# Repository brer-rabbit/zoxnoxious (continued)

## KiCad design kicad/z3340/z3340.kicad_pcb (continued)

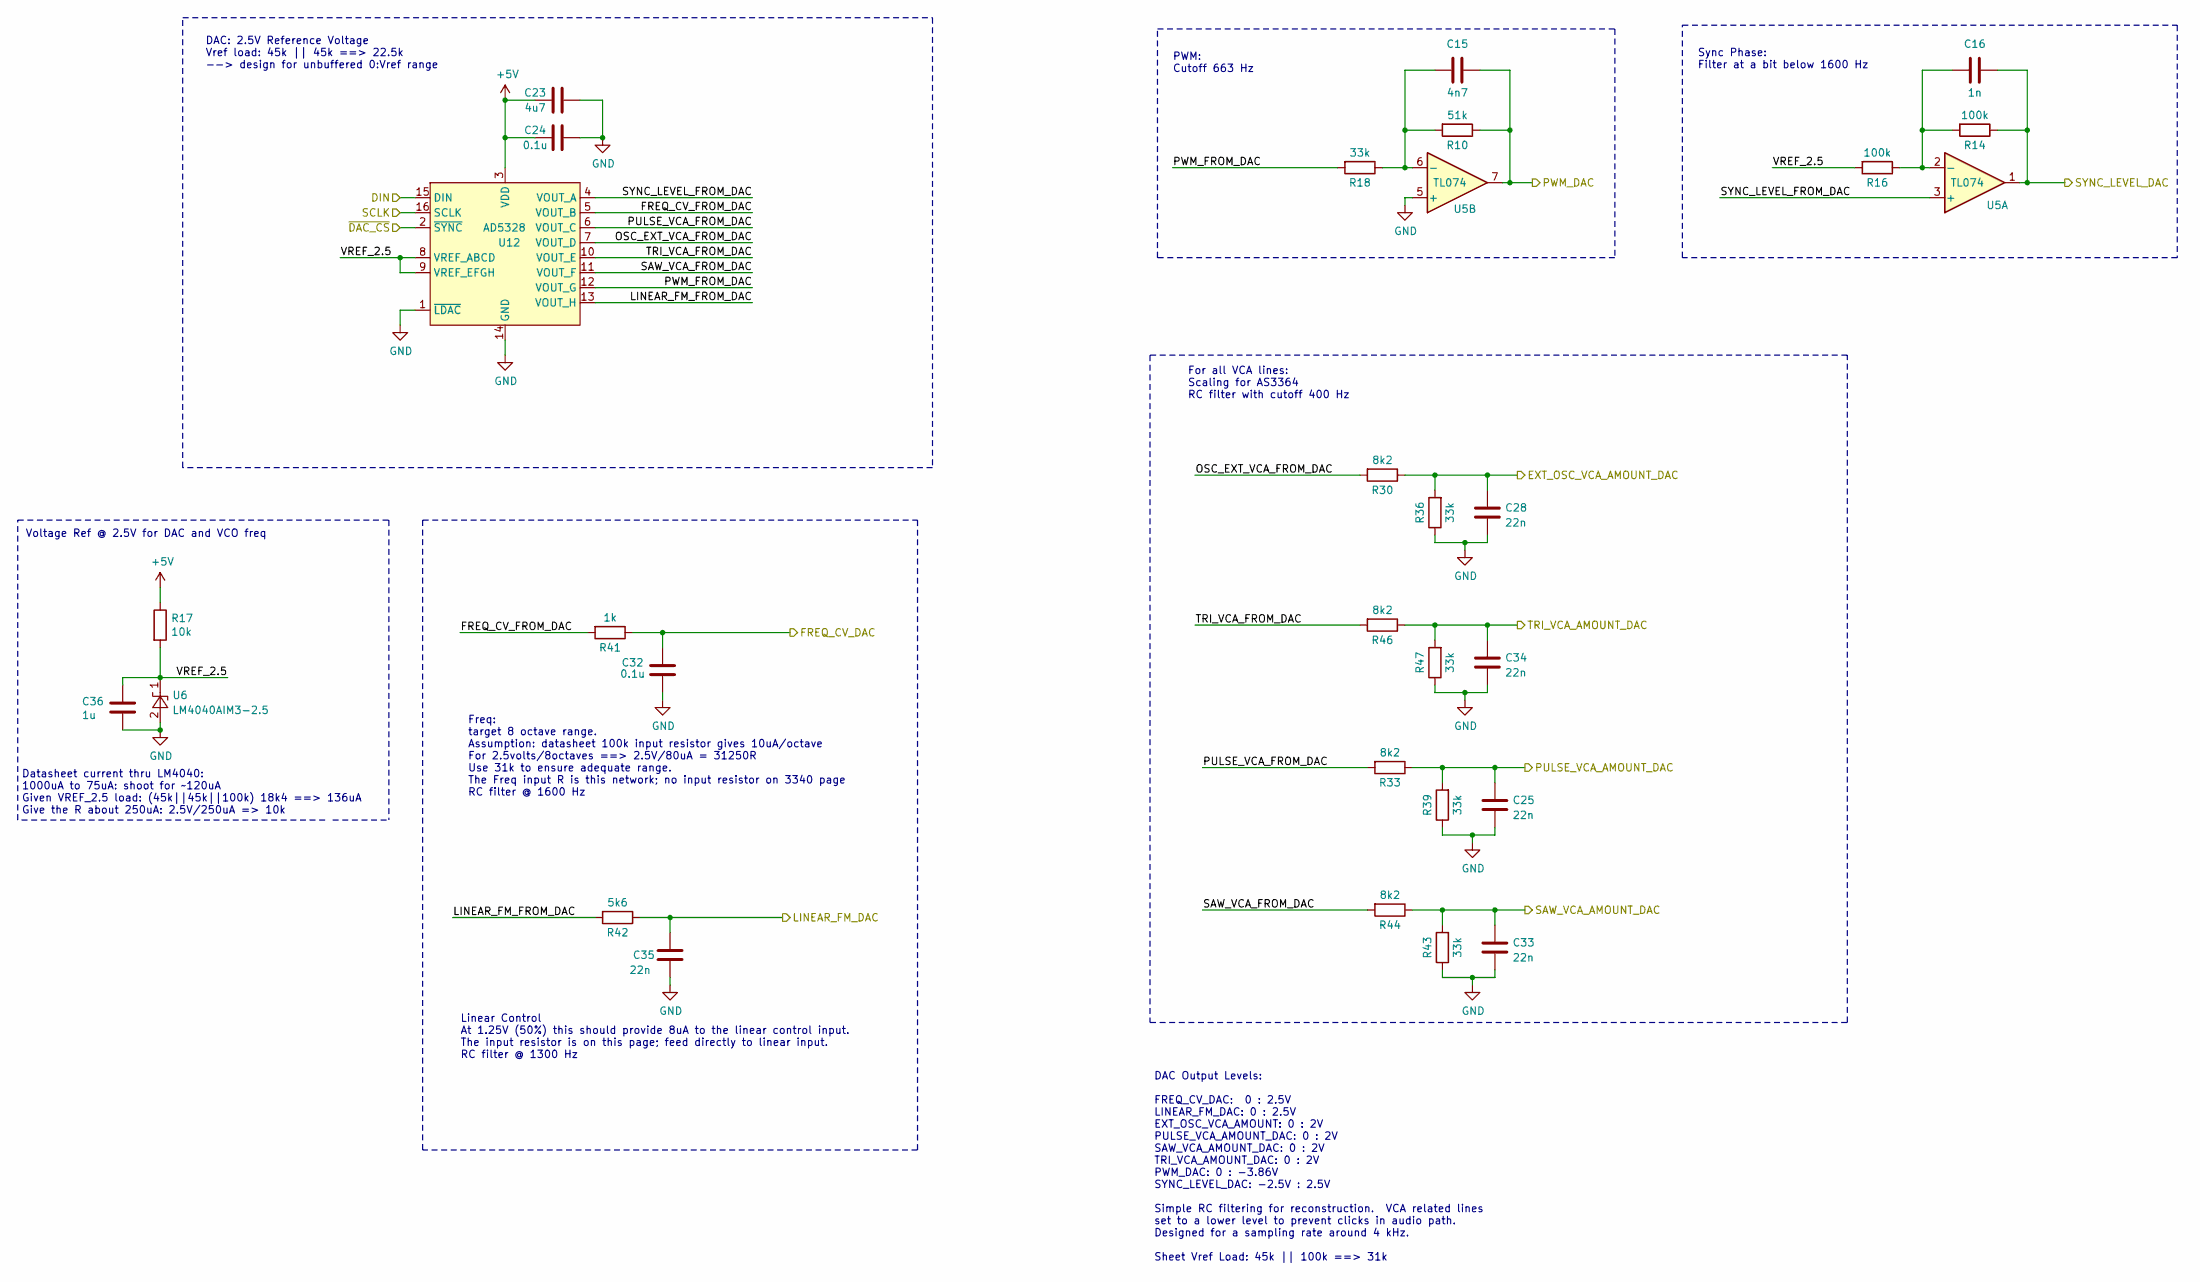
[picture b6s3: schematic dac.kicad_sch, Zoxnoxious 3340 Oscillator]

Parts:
C15: 4n7; C_0603_1608Metric; LCSC C53987
C16: 1n; C_0603_1608Metric; LCSC C1588
C23: 4u7; C_0805_2012Metric; LCSC C1779
C24, C32: 0.1u; C_0603_1608Metric; LCSC C14663
C25, C28, C33, C34, C35: 22n; C_0603_1608Metric; LCSC C21122
C36: 1u; C_0603_1608Metric; LCSC C15849
R10: 51k; R_0603_1608Metric; LCSC C23196
R14, R16: 100k; R_0603_1608Metric; LCSC C25803
R17: 10k; R_0603_1608Metric; LCSC C25804
R18, R36, R39, R43, R47: 33k; R_0603_1608Metric; LCSC C4216
R30, R33, R44, R46: 8k2; R_0603_1608Metric; LCSC C25981
R41: 1k; R_0603_1608Metric; LCSC C21190
R42: 5k6; R_0603_1608Metric; LCSC C23189
U5: TL074; TSSOP-14_4.4x5mm_P0.65mm; LCSC C96507
U6: LM4040AIM3-2.5; SOT-23; LCSC C460725
U12: AD5328; TSSOP-16_4.4x5mm_P0.65mm; LCSC C29162

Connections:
+5V: C23.1, C24.1, R17.1, U12.3 (VDD); also elsewhere on the board
/DAC/FREQ_CV_FROM_DAC: R41.2, U12.5 (VOUT_B)
/DAC/LINEAR_FM_FROM_DAC: R42.2, U12.13 (VOUT_H)
/DAC/OSC_EXT_VCA_FROM_DAC: R30.2, U12.7 (VOUT_D)
/DAC/PULSE_VCA_FROM_DAC: R33.2, U12.6 (VOUT_C)
/DAC/PWM_FROM_DAC: R18.2, U12.12 (VOUT_G)
/DAC/SAW_VCA_FROM_DAC: R44.2, U12.11 (VOUT_F)
/DAC/SYNC_LEVEL_FROM_DAC: U5.3 (+), U12.4 (VOUT_A)
/DAC/TRI_VCA_FROM_DAC: R46.2, U12.10 (VOUT_E)
/DAC/VREF_2.5: C36.1, R16.2, R17.2, U6.1 (K), U12.8 (VREF_ABCD), U12.9 (VREF_EFGH)
/EXT_OSC_VCA_AMOUNT_DAC: C28.1, R30.1, R36.2; also elsewhere on the board
/LINEAR_FM_DAC: C35.2, R42.1; also elsewhere on the board
/OSC_CV_DAC: C32.2, R41.1; also elsewhere on the board
/PULSE_VCA_AMOUNT_DAC: C25.1, R33.1, R39.2; also elsewhere on the board
/PWM_DAC: C15.2, R10.1, U5.7; also elsewhere on the board
/SAW_VCA_AMOUNT_DAC: C33.1, R43.2, R44.1; also elsewhere on the board
/SPI_CLK: U12.16 (SCLK); also elsewhere on the board
/SPI_CS0: U12.2 (~SYNC); also elsewhere on the board
/SPI_MOSI: U12.15 (DIN); also elsewhere on the board
/SYNC_LEVEL_DAC: C16.2, R14.1, U5.1; also elsewhere on the board
/TRI_VCA_AMOUNT_DAC: C34.1, R46.1, R47.2; also elsewhere on the board
GND: C23.2, C24.2, C25.2, C28.2, C32.1, C33.2, C34.2, C35.1, C36.2, R36.1, R39.1, R43.1, R47.1, U5.5 (+), U6.2 (A), U12.1 (~LDAC), U12.14 (GND); also elsewhere on the board
unnamed: C16.1, R14.2, R16.1, U5.2 (-)
unnamed: C15.1, R10.2, R18.1, U5.6 (-)

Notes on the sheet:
Linear Control At 1.25V (50%) this should provide 8uA to the linear control input. The input resistor is on this page; feed directly to linear input. RC filter @ 1300 Hz
Sync Phase: Filter at a bit below 1600 Hz
Voltage Ref @ 2.5V for DAC and VCO freq
PWM: Cutoff 663 Hz
DAC Output Levels: FREQ_CV_DAC: 0 : 2.5V LINEAR_FM_DAC: 0 : 2.5V EXT_OSC_VCA_AMOUNT: 0 : 2V PULSE_VCA_AMOUNT_DAC: 0 : 2V SAW_VCA_AMOUNT_DAC: 0 : 2V TRI_VCA_AMOUNT_DAC: 0 : 2V PWM_DAC: 0 : -3.86V SYNC_LEVEL_DAC: -2.5V : 2.5V Simple RC filtering for reconstruction. VCA related lines set to a lower le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
Datasheet current thru LM4040: 1000uA to 75uA: shoot for ~120uA Given VREF_2.5 load: (45k||45k||100k) 18k4 ==> 136uA Give the R about 250uA: 2.5V/250uA => 10k
Freq: target 8 octave range. Assumption: datasheet 100k input resistor gives 10uA/octave For 2.5volts/8octaves ==> 2.5V/80uA = 31250R Use 31k to ensure adequate range. The Freq input R is this network; no input resistor on 3340 page RC filter @ 1600 Hz
For all VCA lines: Scaling for AS3364 RC filter with cutoff 400 Hz
DAC: 2.5V Reference Voltage Vref load: 45k || 45k ==> 22.5k --> design for unbuffered 0:Vref range

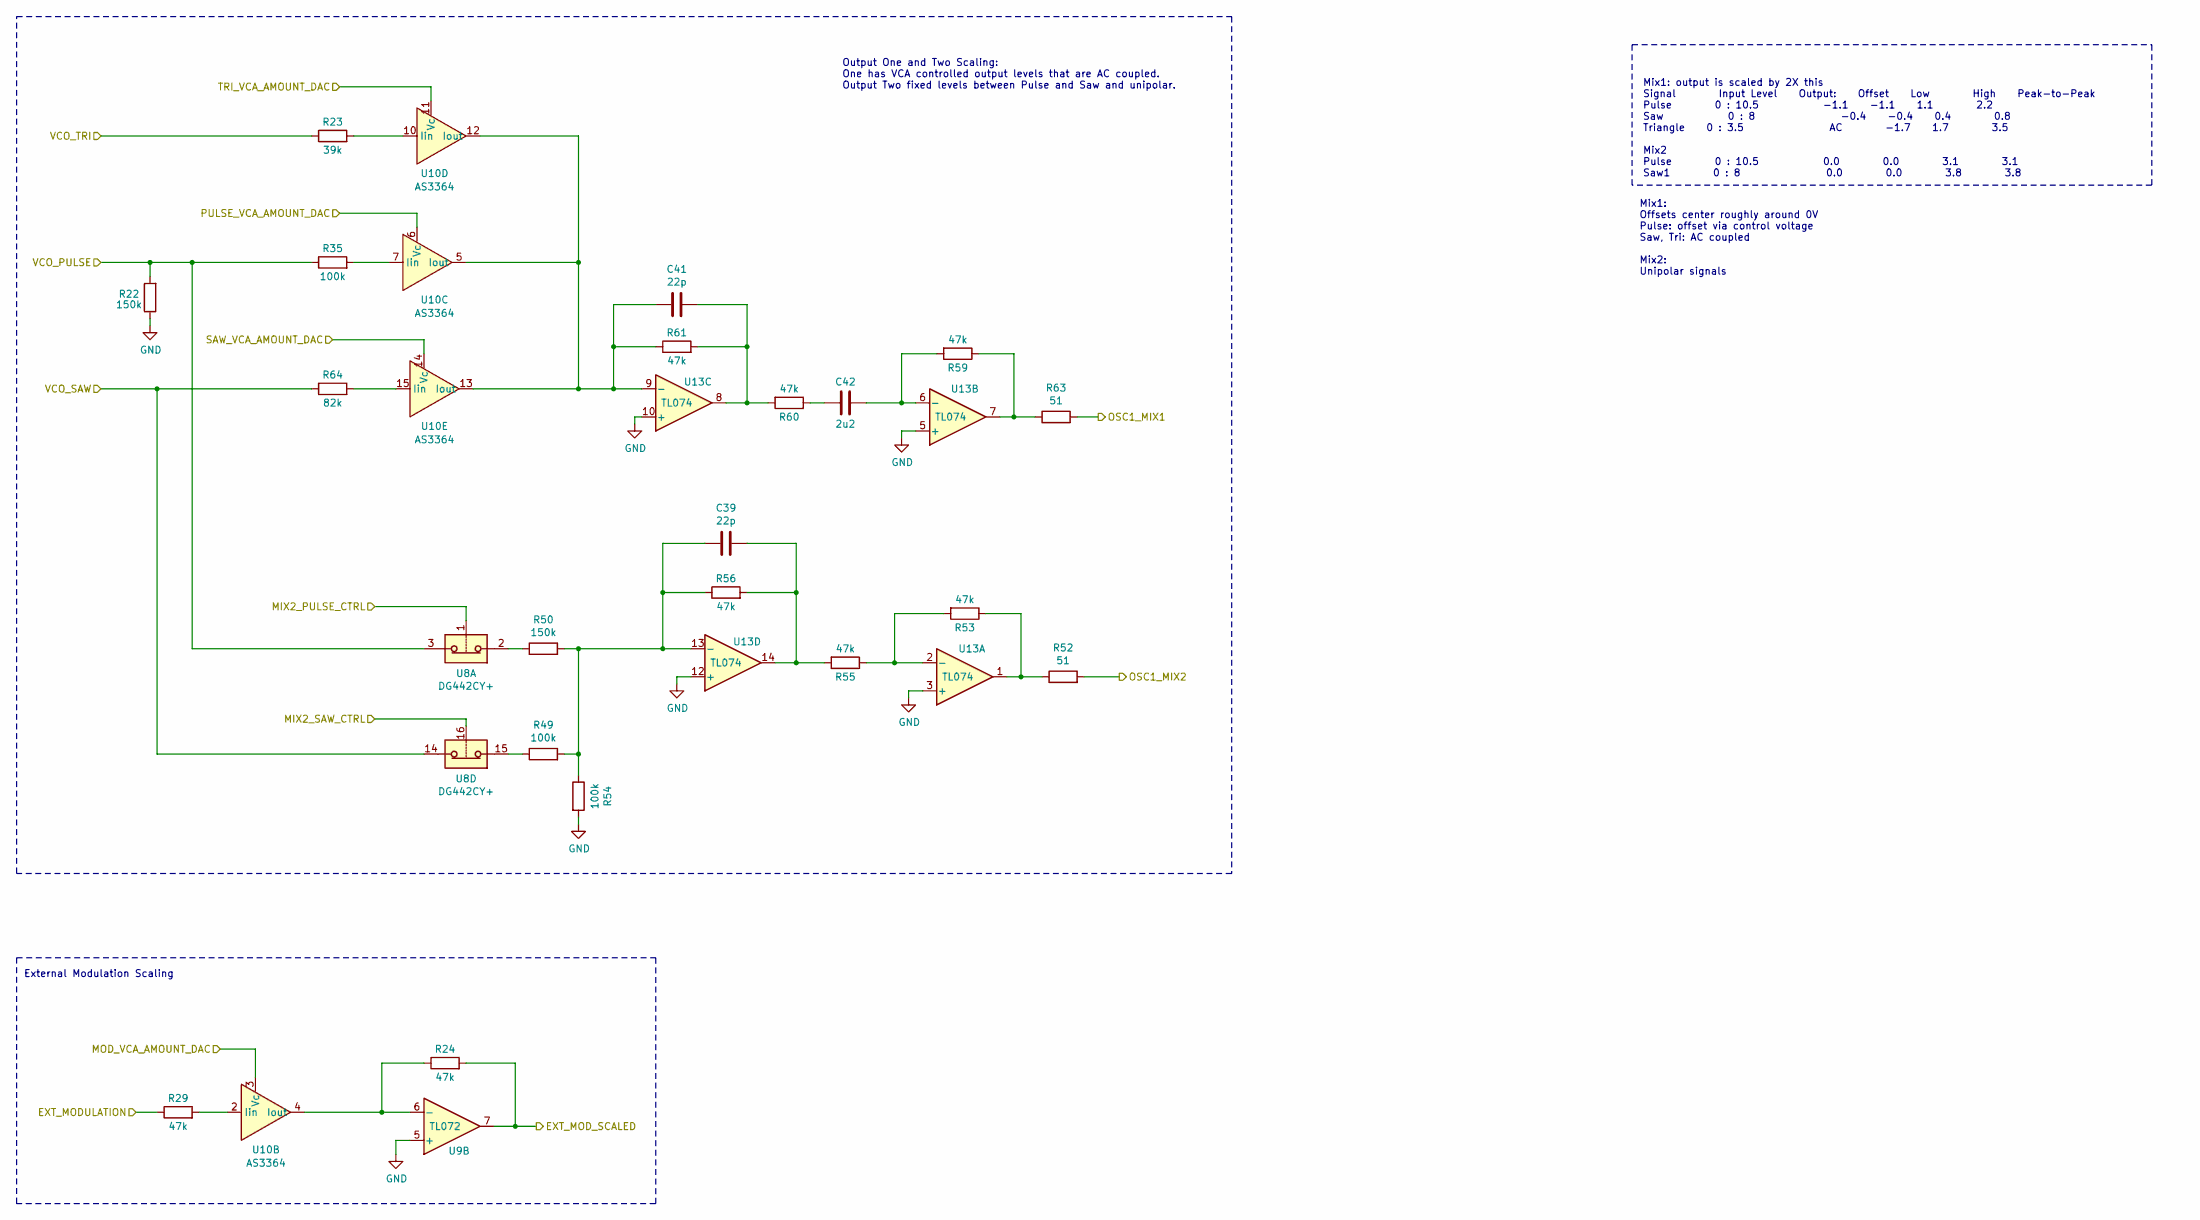
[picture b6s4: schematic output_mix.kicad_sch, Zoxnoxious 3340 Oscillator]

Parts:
C39, C41: 22p; C_0603_1608Metric; LCSC C1653
C42: 2u2; C_Rect_L7.2mm_W5.5mm_P5.00mm_FKS2_FKP2_MKS2_MKP2; Digikey MKS2B042201F00KSSD
R22, R50: 150k; R_0603_1608Metric; LCSC C22807
R23: 39k; R_0603_1608Metric; LCSC C23153
R24, R29, R53, R55, R56, R59, R60, R61: 47k; R_0603_1608Metric; LCSC C25819
R35, R49, R54: 100k; R_0603_1608Metric; LCSC C25803
R52, R63: 51; R_0805_2012Metric; LCSC C17738
R64: 82k; R_0603_1608Metric; LCSC C23254
U8: DG442CY+; SOIC-16_3.9x9.9mm_P1.27mm; Digikey DG442CY+-ND
U9: TL072; SSOP-8_3.9x5.05mm_P1.27mm; LCSC C6961
U10: AS3364; SOIC-16_3.9x9.9mm_P1.27mm
U13: TL074; TSSOP-14_4.4x5mm_P0.65mm; LCSC C96507

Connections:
/EXT_MODULATION: R29.1; also elsewhere on the board
/EXT_MOD_SCALED: R24.2, U9.7; also elsewhere on the board
/EXT_OSC_VCA_AMOUNT_DAC: U10.3 (Vc); also elsewhere on the board
/MIX2_PULSE_CTRL: U8.1; also elsewhere on the board
/MIX2_SAW_CTRL: U8.16; also elsewhere on the board
/PULSE_VCA_AMOUNT_DAC: U10.6 (Vc); also elsewhere on the board
/SAW_VCA_AMOUNT_DAC: U10.14 (Vc); also elsewhere on the board
/THIS_OUT1: R63.2; also elsewhere on the board
/THIS_OUT2: R52.2; also elsewhere on the board
/TRI_VCA_AMOUNT_DAC: U10.11 (Vc); also elsewhere on the board
/VCO_PULSE: R22.2, R35.1, U8.3; also elsewhere on the board
/VCO_SAW: R64.1, U8.14; also elsewhere on the board
/VCO_TRI: R23.1; also elsewhere on the board
GND: R22.1, R54.2, U9.5 (+), U13.3 (+), U13.5 (+), U13.10 (+), U13.12 (+); also elsewhere on the board
unnamed: C39.1, R55.2, R56.2, U13.14
unnamed: C41.1, R60.2, R61.2, U13.8
unnamed: C42.2, R60.1
unnamed: R49.1, U8.15
unnamed: R50.1, U8.2
unnamed: R52.1, R53.1, U13.1
unnamed: R59.1, R63.1, U13.7
unnamed: R29.2, U10.2 (Iin)
unnamed: R24.1, U9.6 (-), U10.4 (Iout)
unnamed: R35.2, U10.7 (Iin)
unnamed: C41.2, R61.1, U10.5 (Iout), U10.12 (Iout), U10.13 (Iout), U13.9 (-)
unnamed: R23.2, U10.10 (Iin)
unnamed: R64.2, U10.15 (Iin)
unnamed: R53.2, R55.1, U13.2 (-)
unnamed: C42.1, R59.2, U13.6 (-)
unnamed: C39.2, R49.2, R50.2, R54.1, R56.1, U13.13 (-)

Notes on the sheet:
Mix1: output is scaled by 2X this Signal Input Level Output: Offset Low High Peak-to-Peak Pulse 0 : 10.5 -1.1 -1.1 1.1 2.2 Saw 0 : 8 -0.4 -0.4 0.4 0.8 Triangle 0 : 3.5 AC -1.7 1.7 3.5 Mix2 Pulse 0 : 10.5 0.0 0.0 3.1 3.1 Saw1 0 : 8 0.0 0.0 3.8 3.8
Output One and Two Scaling: One has VCA controlled output levels that are AC coupled. Output Two fixed levels between Pulse and Saw and unipolar.
Mix1: Offsets center roughly around 0V Pulse: offset via control voltage Saw, Tri: AC coupled Mix2: Unipolar signals
External Modulation Scaling

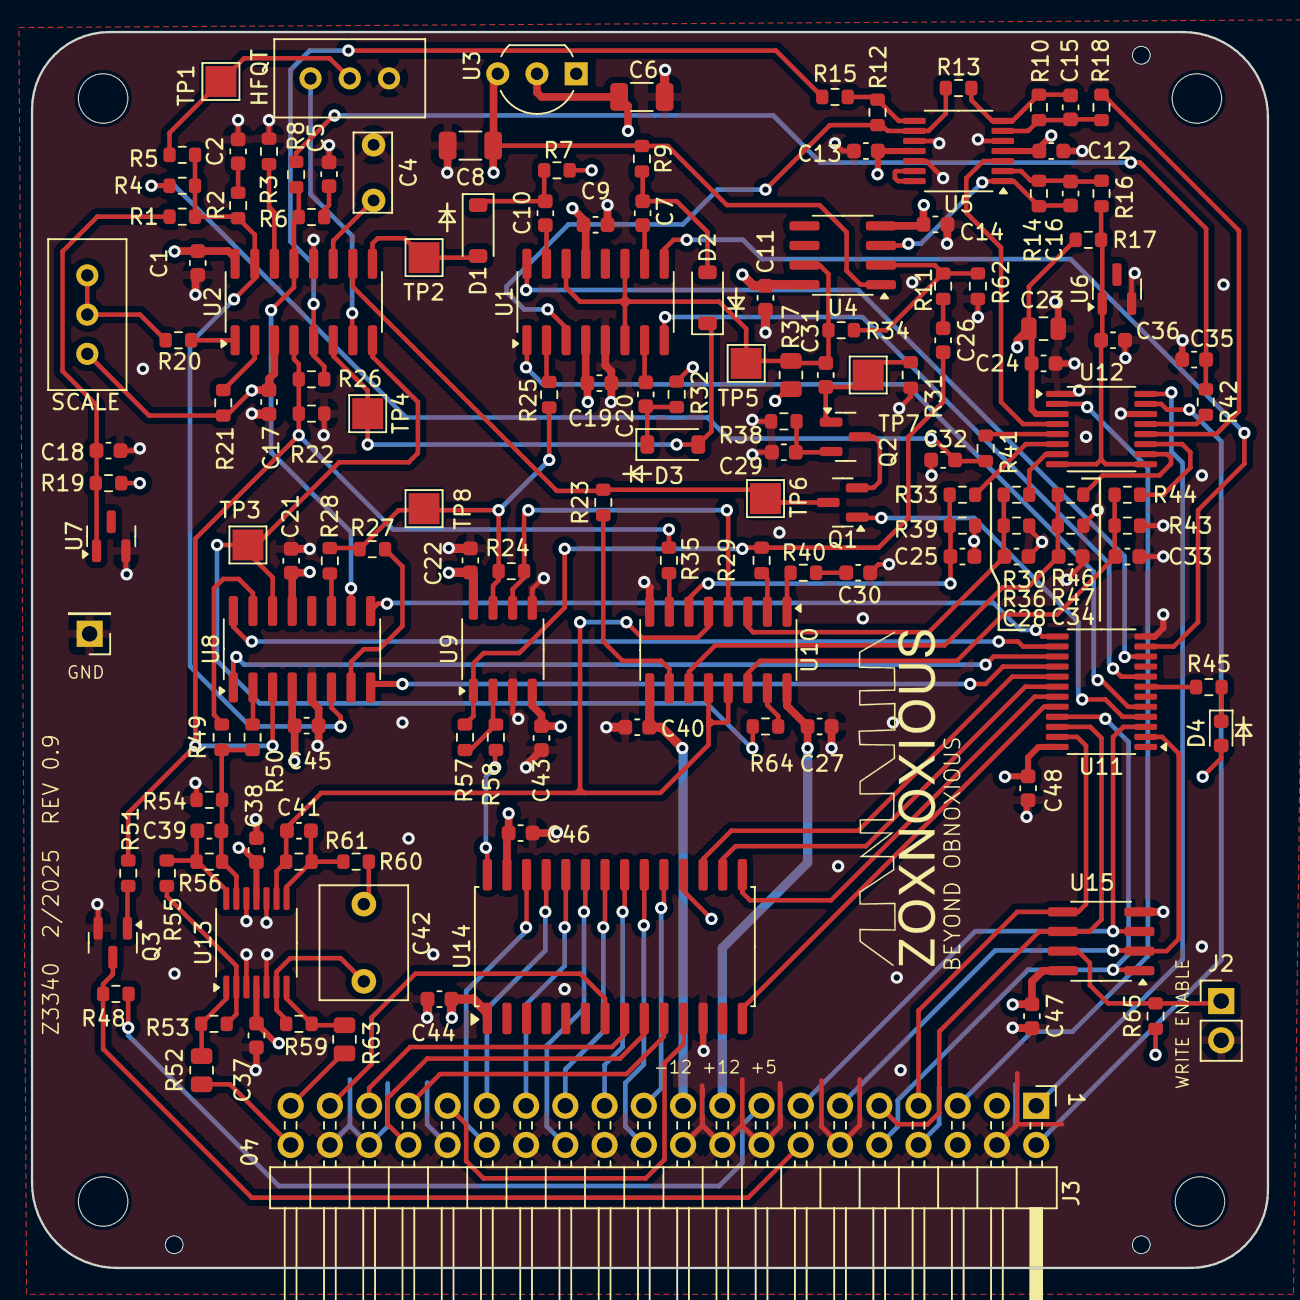
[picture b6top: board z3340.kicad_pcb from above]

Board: 4 copper layers, 80.0 x 80.0 mm, 151 parts (0 on the bottom side), 123 nets.

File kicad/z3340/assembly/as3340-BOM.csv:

Comment,Designator,Footprint,LCSC Part #
"1n","C16","Capacitor_SMD:C_0603_1608Metric","C1588"
"10n","C2,C5,C7,C10,C20","Capacitor_SMD:C_0603_1608Metric","C57112"
"4.7u","C23","Capacitor_SMD:C_0805_2012Metric","C1779"
"22n","C25,C28,C33,C34,C35","Capacitor_SMD:C_0603_1608Metric","C21122"
"4n7","C15,C30","Capacitor_SMD:C_0603_1608Metric","C53987"
"220p","C31","Capacitor_SMD:C_0603_1608Metric","C1603"
"1u","C18,C36","Capacitor_SMD:C_0603_1608Metric","C15849"
"22p","C39,C41","Capacitor_SMD:C_0603_1608Metric","C1653"
"1u","C6,C8","Capacitor_SMD:C_1206_3216Metric","C1848"
"0.1u","C1,C3,C9,C11,C12,C13,C14,C17,C19,C21,C22,C24,C26,C27,C29,C32,C37,C38,C40,C43,C44,C45,C46,C47,C48","Capacitor_SMD:C_0603_1608Metric","C14663"
"1N4148W","D1,D2,D3","Diode_SMD:D_SOD-123","C81598"
"LED","D4","LED_SMD:LED_0603_1608Metric","C2286"
"2N7002","Q1,Q2","Package_TO_SOT_SMD:SOT-23","C8545"
"MMBT3904","Q3","Package_TO_SOT_SMD:SOT-23","C20526"
"120k","R1,R35","Resistor_SMD:R_0603_1608Metric","C25808"
"51k","R10","Resistor_SMD:R_0603_1608Metric","C23196"
"56k","R12,R13","Resistor_SMD:R_0603_1608Metric","C23206"
"12k","R17,R62","Resistor_SMD:R_0603_1608Metric","C22790"
"33k","R18,R19,R36,R39,R43,R47","Resistor_SMD:R_0603_1608Metric","C4216"
"470","R2,R6","Resistor_SMD:R_0603_1608Metric","C23179"
"24k","R20","Resistor_SMD:R_0603_1608Metric","C23352"
"47k","R23,R24,R29,R53,R55,R56,R59,R60,R61","Resistor_SMD:R_0603_1608Metric","C25819"
"82k","R25,R64","Resistor_SMD:R_0603_1608Metric","C23254"
"200k","R27","Resistor_SMD:R_0603_1608Metric","C25811"
"1k8","R3","Resistor_SMD:R_0603_1608Metric","C4177"
"8k2","R30,R33,R37,R44,R46","Resistor_SMD:R_0603_1608Metric","C25981"
"30k","R4","Resistor_SMD:R_0603_1608Metric","C22984"
"100","R38,R40","Resistor_SMD:R_0603_1608Metric","C22775"
"1k","R41","Resistor_SMD:R_0603_1608Metric","C21190"
"5k6","R21,R42","Resistor_SMD:R_0603_1608Metric","C23189"
"2k","R45","Resistor_SMD:R_0603_1608Metric","C22975"
"10k","R7,R9,R11,R15,R31,R32,R48,R65","Resistor_SMD:R_0603_1608Metric","C25804"
"1M","R5,R26,R28,R34","Resistor_SMD:R_0603_1608Metric","C22935"
"100k","R14,R16,R49,R51,R54,R57,R58","Resistor_SMD:R_0603_1608Metric","C25803"
"51","R52,R63","Resistor_SMD:R_0805_2012Metric","C17738"
"150k","R8,R22,R50","Resistor_SMD:R_0603_1608Metric","C22807"
"DG442CY+","U1,U8","Package_SO:SOIC-16_3.9x9.9mm_P1.27mm","C2673321"
"PCA9555D","U11","Package_SO:TSSOP-24_4.4x7.8mm_P0.65mm","C83265"
"AD5328","U12","Package_SO:TSSOP-16_4.4x5mm_P0.65mm","C29162"
"DG406","U14","Package_SO:SOIC-28W_7.5x17.9mm_P1.27mm","C426318"
"M24C02-WMN","U15","Package_SO:SOIC-8_3.9x4.9mm_P1.27mm","C7562"
"LM311","U4","Package_SO:SOIC-8_3.9x4.9mm_P1.27mm","C12597"
"TL074","U5,U13","Package_SO:TSSOP-14_4.4x5mm_P0.65mm","C96507"
"LM4040AIM3-2.5","U6","Package_TO_SOT_SMD:SOT-23","C460725"
"LM4040B-5","U7","Package_TO_SOT_SMD:SOT-23","C69315"
"TL072","U9","Package_SO:SSOP-8_3.9x5.05mm_P1.27mm","C6961"

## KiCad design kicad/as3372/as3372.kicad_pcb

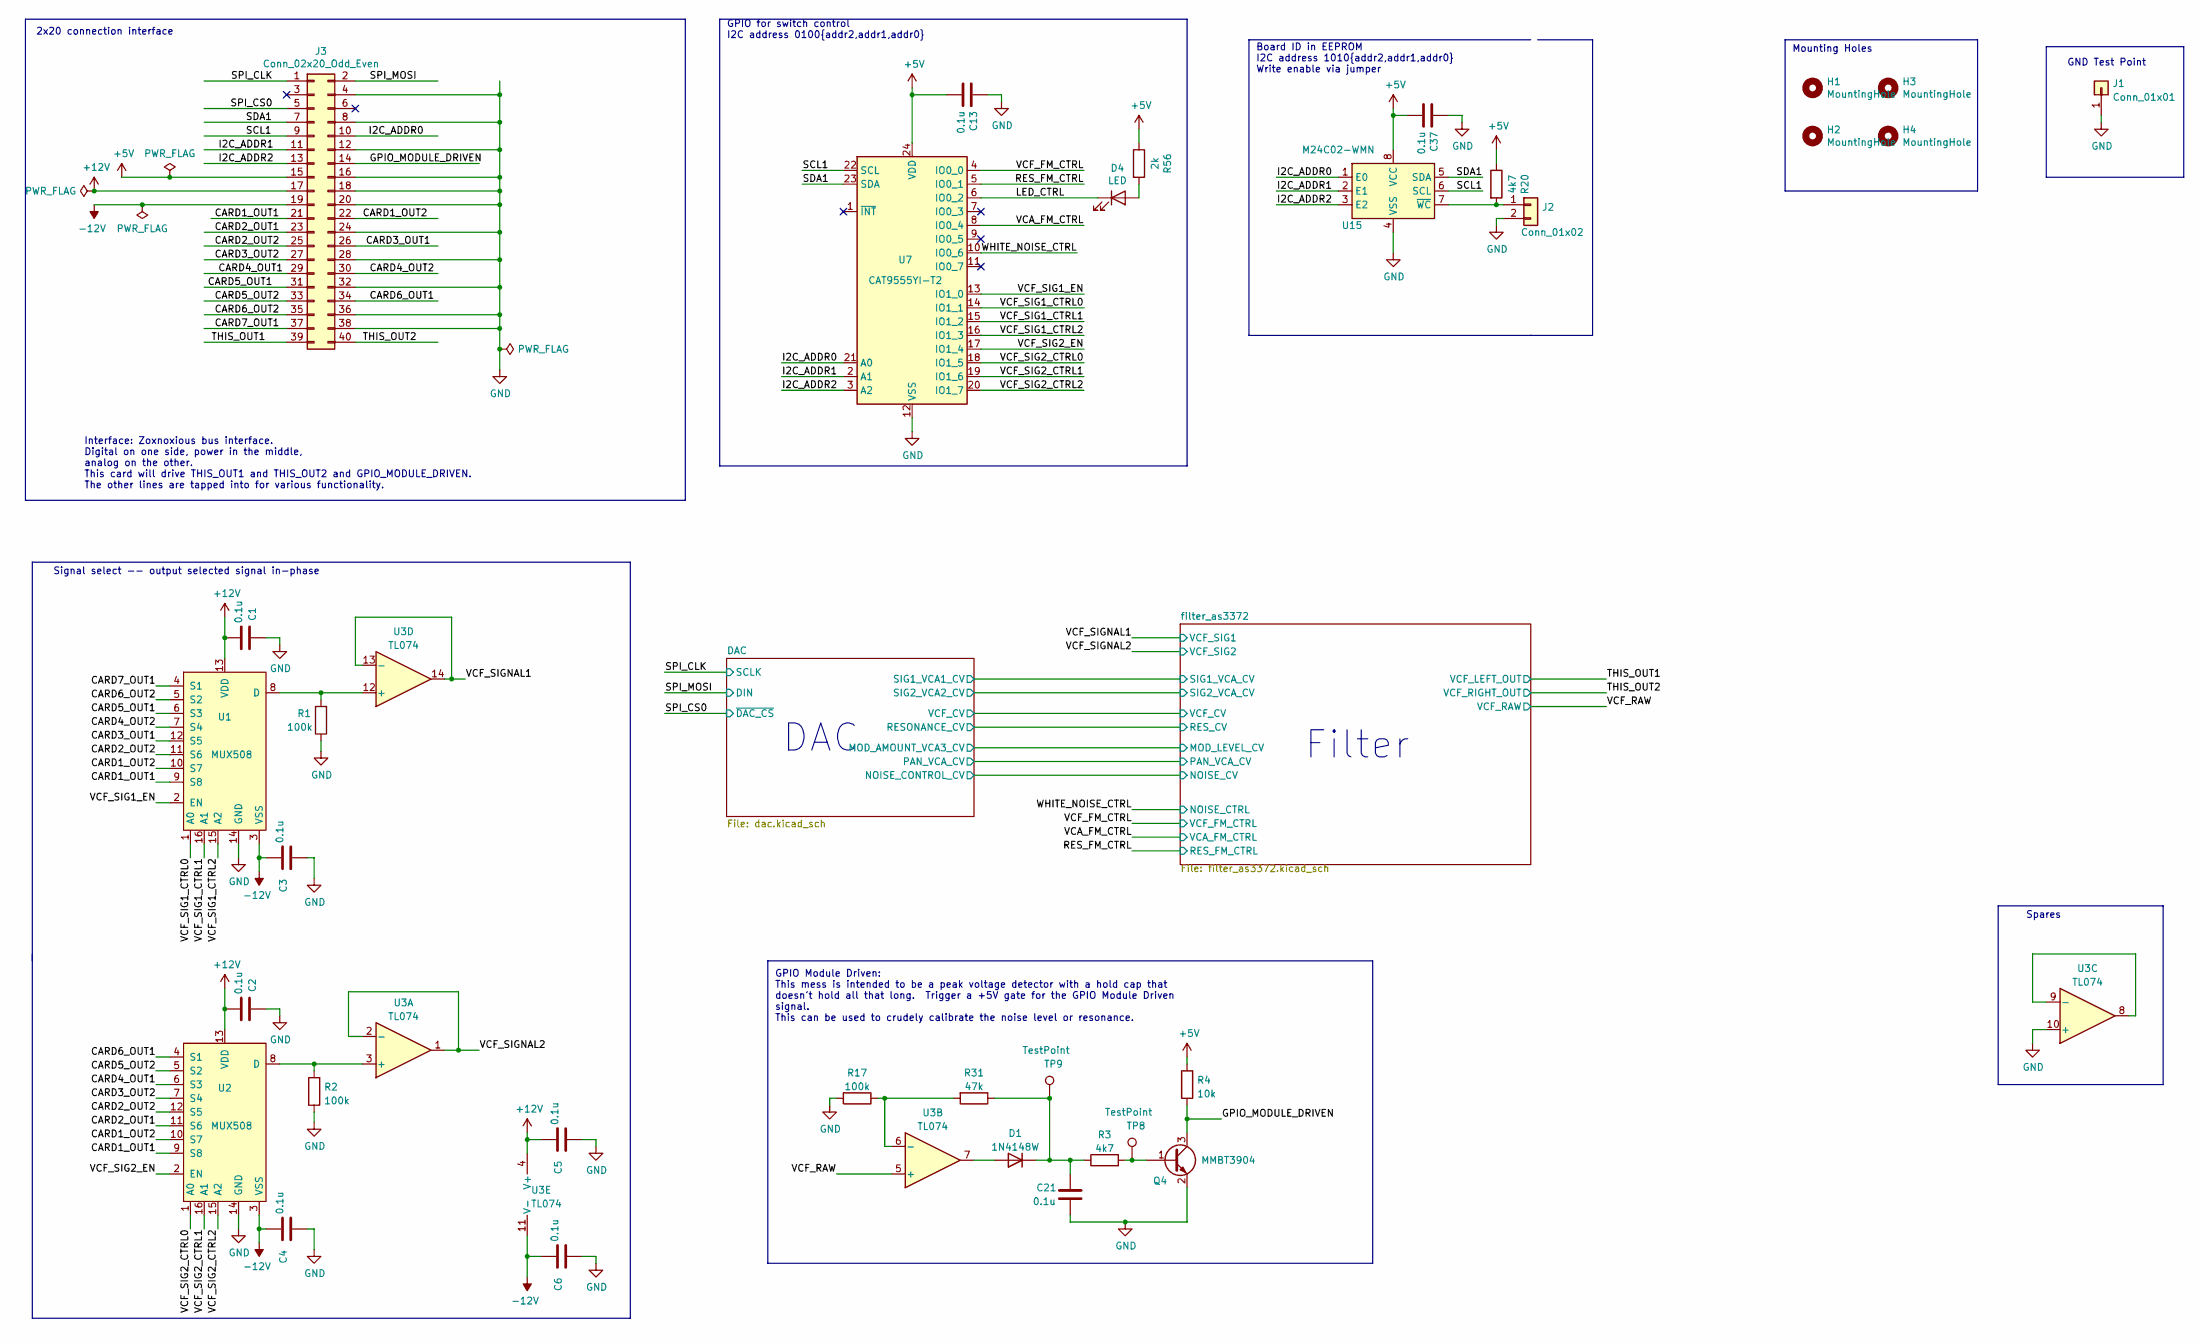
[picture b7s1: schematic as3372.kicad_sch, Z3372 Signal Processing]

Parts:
C1, C2, C3, C4, C5, C6, C13, C21, C37: 0.1u; C_0603_1608Metric; LCSC Part C14663
D1: 1N4148W; D_SOD-123; LCSC Part C81598
D4: LED; LED_0603_1608Metric; LCSC Part C2286
H1, H2, H3, H4: MountingHole; MountingHole_3.2mm_M3
J1: Conn_01x01; PinHeader_1x01_P2.54mm_Vertical
J2: Conn_01x02; PinHeader_1x02_P2.54mm_Vertical
J3: Conn_02x20_Odd_Even; PinHeader_2x20_P2.54mm_Horizontal
Q4: MMBT3904; SOT-23; LCSC Part C20526
R1, R2: 100k; R_0402_1005Metric; LCSC Part C25741
R3, R20: 4k7; R_0603_1608Metric; LCSC Part C23162
R4: 10k; R_0603_1608Metric; LCSC Part C25804
R17: 100k; R_0603_1608Metric; LCSC Part C25803
R31: 47k; R_0603_1608Metric; LCSC Part C25819
R56: 2k; R_0603_1608Metric; LCSC Part C22975
TP8, TP9: TestPoint; TestPoint_Pad_2.0x2.0mm
U1, U2: MUX508; SOIC-16_3.9x9.9mm_P1.27mm; LCSC Part C2673104
U3: TL074; SOIC-14_3.9x8.7mm_P1.27mm; LCSC Part C12594
U7: CAT9555YI-T2; TSSOP-24_4.4x7.8mm_P0.65mm; LCSC Part C83265
U15: M24C02-WMN; SOIC-8_3.9x4.9mm_P1.27mm; LCSC Part C7562

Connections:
+5V: C13.2, C37.2, J3.15, R4.2, R20.1, R56.1, U7.24 (VDD), U15.8 (VCC); also elsewhere on the board
+12V: C1.2, C2.2, C5.2, J3.17, U1.13 (VDD), U2.13 (VDD), U3.4 (V+); also elsewhere on the board
-12V: C3.2, C4.2, C6.2, J3.19, U1.3 (VSS), U2.3 (VSS), U3.11 (V-); also elsewhere on the board
/CARD1_OUT1: J3.21, U1.9 (S8), U2.9 (S8)
/CARD1_OUT2: J3.22, U1.10 (S7), U2.10 (S7)
/CARD2_OUT1: J3.23, U2.11 (S6)
/CARD2_OUT2: J3.25, U1.11 (S6), U2.12 (S5)
/CARD3_OUT1: J3.26, U1.12 (S5)
/CARD3_OUT2: J3.27, U2.7 (S4)
/CARD4_OUT1: J3.29, U2.6 (S3)
/CARD4_OUT2: J3.30, U1.7 (S4)
/CARD5_OUT1: J3.31, U1.6 (S3)
/CARD5_OUT2: J3.33, U2.5 (S2)
/CARD6_OUT1: J3.34, U2.4 (S1)
/CARD6_OUT2: J3.35, U1.5 (S2)
/CARD7_OUT1: J3.37, U1.4 (S1)
/GPIO_MODULE_DRIVEN: J3.14, Q4.3 (C), R4.1
/I2C_ADDR0: J3.10, U7.21 (A0), U15.1 (E0)
/I2C_ADDR1: J3.11, U7.2 (A1), U15.2 (E1)
/I2C_ADDR2: J3.13, U7.3 (A2), U15.3 (E2)
/LED_CTRL: D4.1 (K), U7.6 (IO0_2)
/RES_FM_CTRL: U7.5 (IO0_1); also elsewhere on the board
/SCL1: J3.9, U7.22 (SCL), U15.6 (SCL)
/SDA1: J3.7, U7.23 (SDA), U15.5 (SDA)
/SPI_CLK: J3.1; also elsewhere on the board
/SPI_CS0: J3.5; also elsewhere on the board
/SPI_MOSI: J3.2; also elsewhere on the board
/THIS_OUT1: J3.39; also elsewhere on the board
/THIS_OUT2: J3.40; also elsewhere on the board
/VCA_FM_CTRL: U7.8 (IO0_4); also elsewhere on the board
/VCF_FM_CTRL: U7.4 (IO0_0); also elsewhere on the board
/VCF_RAW: U3.5 (+); also elsewhere on the board
/VCF_SIG1_CTRL0: U1.1 (A0), U7.14 (IO1_1)
/VCF_SIG1_CTRL1: U1.16 (A1), U7.15 (IO1_2)
/VCF_SIG1_CTRL2: U1.15 (A2), U7.16 (IO1_3)
/VCF_SIG1_EN: U1.2 (EN), U7.13 (IO1_0)
/VCF_SIG2_CTRL0: U2.1 (A0), U7.18 (IO1_5)
/VCF_SIG2_CTRL1: U2.16 (A1), U7.19 (IO1_6)
/VCF_SIG2_CTRL2: U2.15 (A2), U7.20 (IO1_7)
/VCF_SIG2_EN: U2.2 (EN), U7.17 (IO1_4)
/VCF_SIGNAL1: U3.13 (-), U3.14; also elsewhere on the board
/VCF_SIGNAL2: U3.1, U3.2 (-); also elsewhere on the board
/WHITE_NOISE_CTRL: U7.10 (IO0_6); also elsewhere on the board
GND: C1.1, C2.1, C3.1, C4.1, C5.1, C6.1, C13.1, C21.2, C37.1, J1.1, J2.2, J3.4, J3.8, J3.12, J3.16, J3.18, J3.20, J3.24, J3.28, J3.32, J3.36, J3.38, Q4.2 (E), R1.1, R2.1, R17.2, U1.14 (GND), U2.14 (GND), U3.10 (+), U7.12 (VSS), U15.4 (VSS); also elsewhere on the board
unnamed: C21.1, D1.1 (K), R3.1, R31.1, TP9.1
unnamed: D1.2 (A), U3.7
unnamed: D4.2 (A), R56.2
unnamed: J2.1, R20.2, U15.7 (~WC)
unnamed: Q4.1 (B), R3.2, TP8.1
unnamed: R1.2, U1.8 (D), U3.12 (+)
unnamed: R2.2, U2.8 (D), U3.3 (+)
unnamed: R17.1, R31.2, U3.6 (-)
unnamed: U3.8, U3.9 (-)

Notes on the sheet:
Filter
Signal select -- output selected signal in-phase
2x20 connection interface
GPIO Module Driven: This mess is intended to be a peak voltage detector with a hold cap that doesn't hold all that long. Trigger a +5V gate for the GPIO Module Driven signal. This can be used to crudely calibrate the noise level or resonance.
GPIO for switch control I2C address 0100{addr2,addr1,addr0}
Mounting Holes
Spares
GND Test Point
Board ID in EEPROM I2C address 1010{addr2,addr1,addr0} Write enable via jumper
Interface: Zoxnoxious bus interface. Digital on one side, power in the middle, analog on the other. This card will drive THIS_OUT1 and THIS_OUT2 and GPIO_MODULE_DRIVEN. The other lines are tapped into for various functionality.
DAC

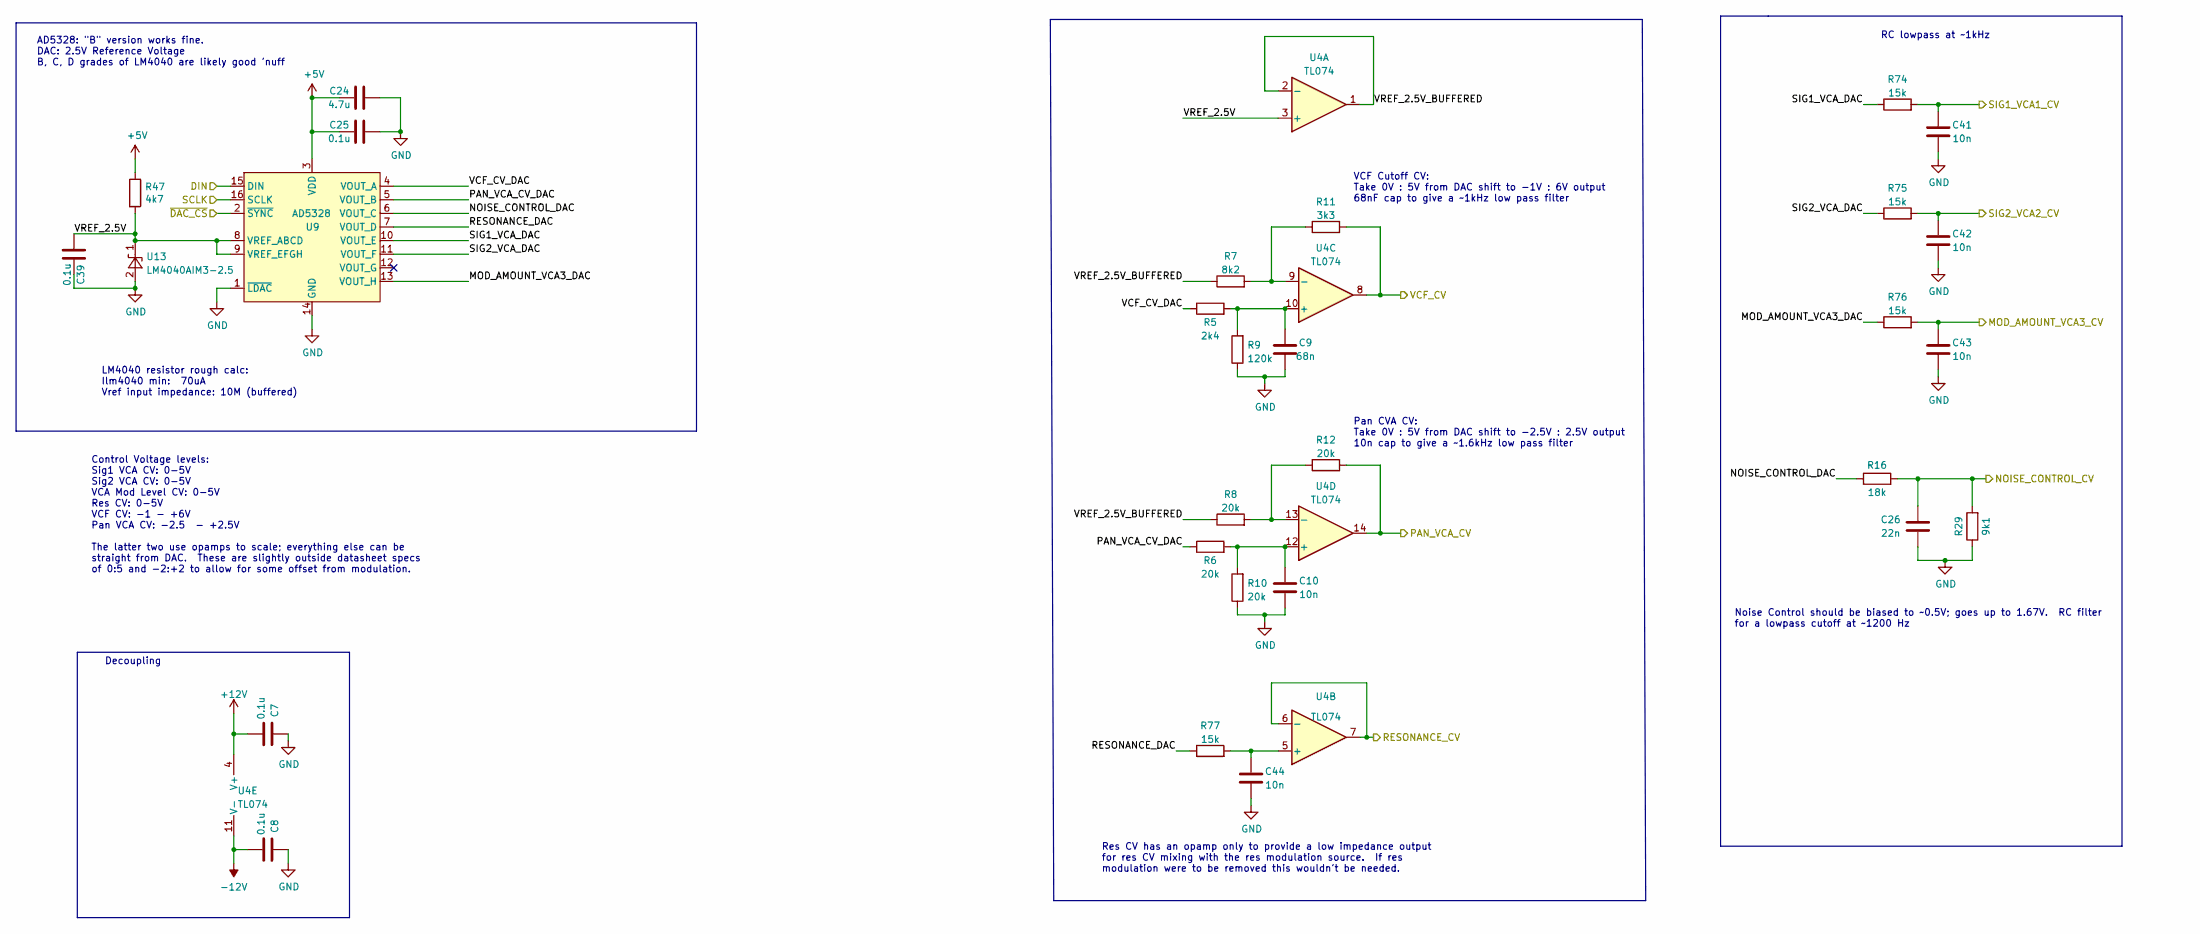
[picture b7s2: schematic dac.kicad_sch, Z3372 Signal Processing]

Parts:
C7, C8, C25, C39: 0.1u; C_0603_1608Metric; LCSC Part C14663
C9: 68n; C_0603_1608Metric; LCSC Part C31658
C10, C41, C42, C43, C44: 10n; C_0603_1608Metric; LCSC Part C57112
C24: 4.7u; C_0805_2012Metric; LCSC Part C1779
C26: 22n; C_0805_2012Metric; LCSC Part C21122
R5: 2k4; R_0603_1608Metric; LCSC Part C22940
R6, R8, R10, R12: 20k; R_0603_1608Metric; LCSC Part C4184
R7: 8k2; R_0603_1608Metric; LCSC Part C25981
R9: 120k; R_0603_1608Metric; LCSC Part C25808
R11: 3k3; R_0603_1608Metric; LCSC Part C22978
R16: 18k; R_0603_1608Metric; LCSC Part C25810
R29: 9k1; R_0603_1608Metric; LCSC Part C23260
R47: 4k7; R_1206_3216Metric; LCSC Part C17936
R74, R75, R76, R77: 15k; R_0603_1608Metric; LCSC Part C22809
U4: TL074; SOIC-14_3.9x8.7mm_P1.27mm; LCSC Part C6963
U9: AD5328; TSSOP-16_4.4x5mm_P0.65mm; LCSC Part C29162
U13: LM4040AIM3-2.5; SOT-23; LCSC Part C460725

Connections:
+5V: C24.1, C25.1, R47.1, U9.3 (VDD); also elsewhere on the board
+12V: C7.2, U4.4 (V+); also elsewhere on the board
-12V: C8.2, U4.11 (V-); also elsewhere on the board
/DAC/MOD_AMOUNT_VCA3_CV: C43.1, R76.2; also elsewhere on the board
/DAC/MOD_AMOUNT_VCA3_DAC: R76.1, U9.13 (VOUT_H)
/DAC/NOISE_CONTROL_CV: C26.1, R16.2, R29.2; also elsewhere on the board
/DAC/NOISE_CONTROL_DAC: R16.1, U9.6 (VOUT_C)
/DAC/PAN_VCA_CV: R12.2, U4.14; also elsewhere on the board
/DAC/PAN_VCA_CV_DAC: R6.1, U9.5 (VOUT_B)
/DAC/RESONANCE_CV: U4.6 (-), U4.7; also elsewhere on the board
/DAC/RESONANCE_DAC: R77.1, U9.7 (VOUT_D)
/DAC/SIG1_VCA1_CV: C41.1, R74.2; also elsewhere on the board
/DAC/SIG1_VCA_DAC: R74.1, U9.10 (VOUT_E)
/DAC/SIG2_VCA2_CV: C42.1, R75.2; also elsewhere on the board
/DAC/SIG2_VCA_DAC: R75.1, U9.11 (VOUT_F)
/DAC/VCF_CV: R11.2, U4.8; also elsewhere on the board
/DAC/VCF_CV_DAC: R5.1, U9.4 (VOUT_A)
/DAC/VREF_2.5V: C39.1, R47.2, U4.3 (+), U9.8 (VREF_ABCD), U9.9 (VREF_EFGH), U13.1 (K)
/DAC/VREF_2.5V_BUFFERED: R7.1, R8.1, U4.1, U4.2 (-)
/SPI_CLK: U9.16 (SCLK); also elsewhere on the board
/SPI_CS0: U9.2 (~SYNC); also elsewhere on the board
/SPI_MOSI: U9.15 (DIN); also elsewhere on the board
GND: C7.1, C8.1, C9.2, C10.2, C24.2, C25.2, C26.2, C39.2, C41.2, C42.2, C43.2, C44.2, R9.1, R10.1, R29.1, U9.1 (~LDAC), U9.14 (GND), U13.2 (A); also elsewhere on the board
unnamed: C9.1, R5.2, R9.2, U4.10 (+)
unnamed: C10.1, R6.2, R10.2, U4.12 (+)
unnamed: C44.1, R77.2, U4.5 (+)
unnamed: R7.2, R11.1, U4.9 (-)
unnamed: R8.2, R12.1, U4.13 (-)

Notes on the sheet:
RC lowpass at ~1kHz
VCF Cutoff CV: Take 0V : 5V from DAC shift to -1V : 6V output 68nF cap to give a ~1kHz low pass filter
Pan CVA CV: Take 0V : 5V from DAC shift to -2.5V : 2.5V output 10n cap to give a ~1.6kHz low pass filter
LM4040 resistor rough calc: Ilm4040 min: 70uA Vref input impedance: 10M (buffered)
Noise Control should be biased to ~0.5V; goes up to 1.67V. RC filter for a lowpass cutoff at ~1200 Hz
Res CV has an opamp only to provide a low impedance output for res CV mixing with the res modulation source. If res modulation were to be removed this wouldn't be needed.
Control Voltage levels: Sig1 VCA CV: 0-5V Sig2 VCA CV: 0-5V VCA Mod Level CV: 0-5V Res CV: 0-5V VCF CV: -1 - +6V Pan VCA CV: -2.5 - +2.5V The latter two use opamps to scale; everything else can be straight from DAC. These are slightly outside datasheet specs of 0:5 and -2:+2 to allow for some offse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
Decoupling
AD5328: "B" version works fine. DAC: 2.5V Reference Voltage B, C, D grades of LM4040 are likely good 'nuff
